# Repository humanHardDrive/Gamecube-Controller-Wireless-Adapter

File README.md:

# GameCube Wireless Controller Hub
The GameCube Wireless Controller hub allows 4 GameCube controllers to be made wireless to any GameCube controller interface. The hub functions in two halves, one to connect to the controllers, and one to connect to the console. Both halves are based on the RP2040 microcontroller and the NRF24l01 transceiver and share the same source code.

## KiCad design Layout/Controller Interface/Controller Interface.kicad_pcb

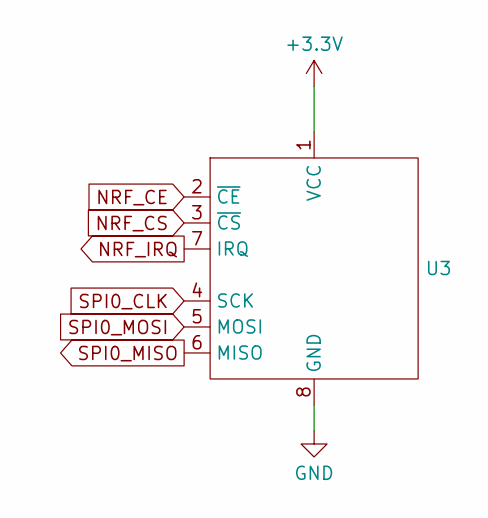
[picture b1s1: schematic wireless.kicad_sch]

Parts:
U3: GTS24-SMD

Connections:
+3.3V: U3.1 (VCC); also elsewhere on the board
GND: U3.8 (GND); also elsewhere on the board
NRF_CE: U3.2 (~CE); also elsewhere on the board
NRF_CS: U3.3 (~CS); also elsewhere on the board
NRF_IRQ: U3.7 (IRQ); also elsewhere on the board
SPI0_CLK: U3.4 (SCK); also elsewhere on the board
SPI0_MISO: U3.6 (MISO); also elsewhere on the board
SPI0_MOSI: U3.5 (MOSI); also elsewhere on the board

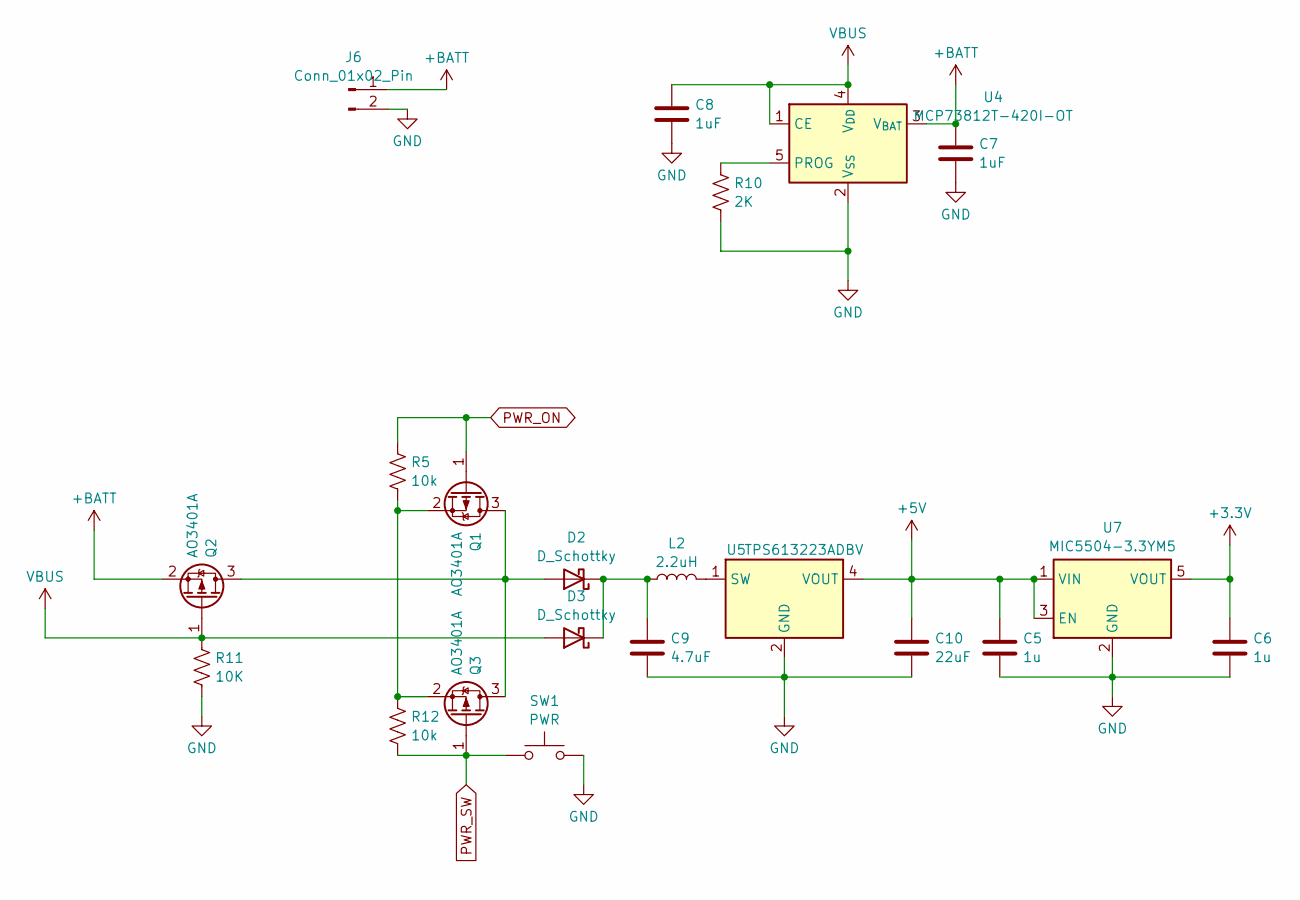
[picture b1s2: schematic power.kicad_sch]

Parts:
C5, C6: 1u; C_0603_1608Metric
C7, C8: 1uF; C_0603_1608Metric
C9: 4.7uF; C_0603_1608Metric
C10: 22uF; C_0603_1608Metric
D2, D3: D_Schottky; D_0805_2012Metric
J6: Conn_01x02_Pin; JST_PH_S2B-PH-SM4-TB_1x02-1MP_P2.00mm_Horizontal
L2: 2.2uH; L_0805_2012Metric
Q1, Q2, Q3: AO3401A; SOT-23
R5, R12: 10k; R_0603_1608Metric
R10: 2K; R_0603_1608Metric
R11: 10K; R_0603_1608Metric
SW1: PWR; Panasonic_EVQPUK_EVQPUB
U4: MCP73812T-420I-OT; SOT-23-5
U5: TPS613223ADBV; SOT-23-5
U7: MIC5504-3.3YM5; SOT-23-5

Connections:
+3.3V: C6.1, U7.5 (VOUT); also elsewhere on the board
+5V: C5.1, C10.1, U5.4 (VOUT), U7.1 (VIN), U7.3 (EN); also elsewhere on the board
+BATT: C7.1, J6.1, Q2.2 (S), U4.3 (V_{BAT})
GND: C5.2, C6.2, C7.2, C8.2, C9.2, C10.2, J6.2, R10.2, R11.1, SW1.2, U4.2 (V_{SS}), U5.2 (GND), U7.2 (GND); also elsewhere on the board
unnamed: D2.2 (A), Q1.3 (D), Q2.3 (D), Q3.3 (D)
unnamed: C9.1, D2.1 (K), D3.1 (K), L2.1
unnamed: Q1.2 (S), Q3.2 (S), R5.2, R12.1
unnamed: R10.1, U4.5 (PROG)
unnamed: L2.2, U5.1 (SW)
PWR_ON: Q1.1 (G), R5.1; also elsewhere on the board
PWR_SW: Q3.1 (G), R12.2, SW1.1; also elsewhere on the board
VBUS: C8.1, D3.2 (A), Q2.1 (G), R11.2, U4.1 (CE), U4.4 (V_{DD}); also elsewhere on the board

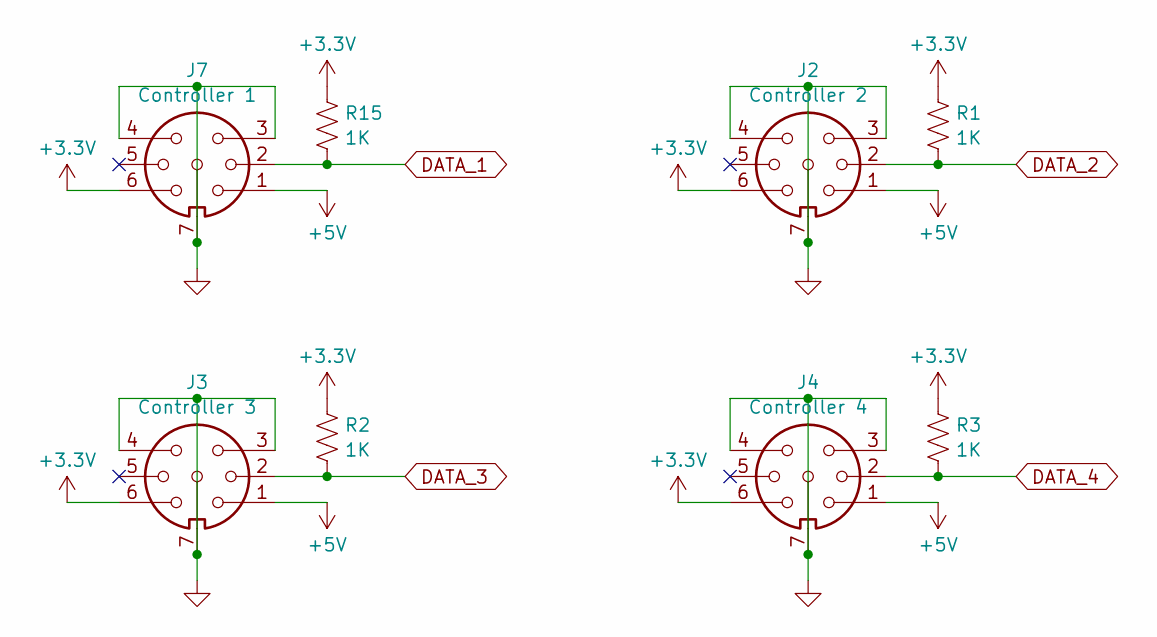
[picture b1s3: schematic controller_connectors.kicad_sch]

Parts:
J2: Controller 2; Gamecube Controller Socket
J3: Controller 3; Gamecube Controller Socket
J4: Controller 4; Gamecube Controller Socket
J7: Controller 1; Gamecube Controller Socket
R1, R2, R3, R15: 1K; R_0603_1608Metric

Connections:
+3.3V: J2.6, J3.6, J4.6, J7.6, R1.1, R2.1, R3.1, R15.1; also elsewhere on the board
+5V: J2.1, J3.1, J4.1, J7.1; also elsewhere on the board
DATA_1: J7.2, R15.2; also elsewhere on the board
DATA_2: J2.2, R1.2; also elsewhere on the board
DATA_3: J3.2, R2.2; also elsewhere on the board
DATA_4: J4.2, R3.2; also elsewhere on the board
GND: J2.3, J2.4, J2.7, J3.3, J3.4, J3.7, J4.3, J4.4, J4.7, J7.3, J7.4, J7.7; also elsewhere on the board

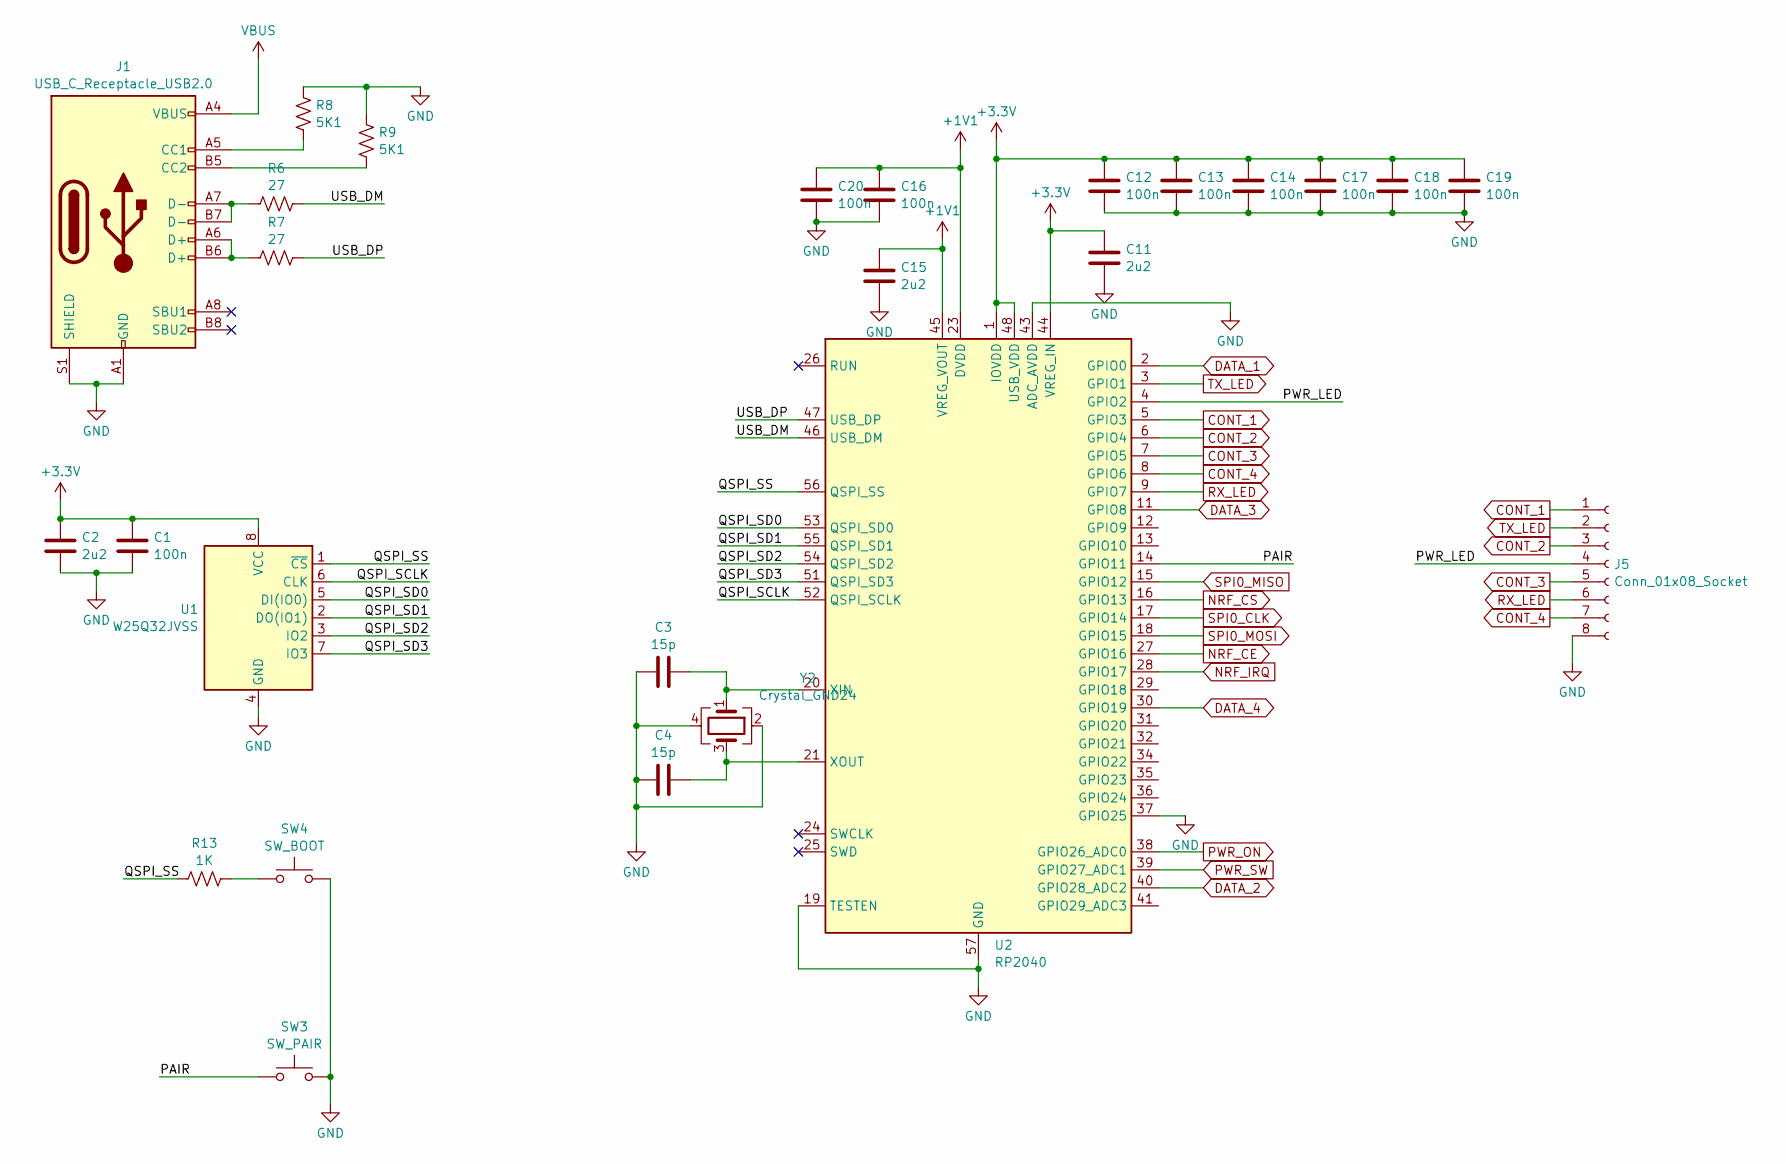
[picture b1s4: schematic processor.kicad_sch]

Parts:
C1, C12, C13, C14, C16, C17, C18, C19, C20: 100n; C_0603_1608Metric
C2, C11, C15: 2u2; C_0603_1608Metric
C3, C4: 15p; C_0603_1608Metric
J1: USB_C_Receptacle_USB2.0; USB_C_Receptacle_GCT_USB4105-xx-A_16P_TopMnt_Horizontal
J5: Conn_01x08_Socket; PinSocket_2x04_P1.00mm_Vertical_SMD
R6, R7: 27; R_0603_1608Metric
R8, R9: 5K1; R_0603_1608Metric
R13: 1K; R_0603_1608Metric
SW3: SW_PAIR; Panasonic_EVQPUK_EVQPUB
SW4: SW_BOOT; SW_SPST_TL3342
U1: W25Q32JVSS; SOIC-8_5.23x5.23mm_P1.27mm
U2: RP2040; QFN-56-1EP_7x7mm_P0.4mm_EP3.2x3.2mm
Y2: Crystal_GND24; Crystal_SMD_Abracon_ABM8G-4Pin_3.2x2.5mm

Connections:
+1V1: C15.1, C16.1, C20.1, U2.23 (DVDD), U2.45 (VREG_VOUT), U2.50 (DVDD)
+3.3V: C1.1, C2.1, C11.1, C12.1, C13.1, C14.1, C17.1, C18.1, C19.1, U1.8 (VCC), U2.1 (IOVDD), U2.10 (IOVDD), U2.22 (IOVDD), U2.33 (IOVDD), U2.42 (IOVDD), U2.44 (VREG_IN), U2.48 (USB_VDD), U2.49 (IOVDD); also elsewhere on the board
/Processor/PAIR: SW3.1, U2.14 (GPIO11)
/Processor/PWR_LED: J5.4, U2.4 (GPIO2)
/Processor/QSPI_SCLK: U1.6 (CLK), U2.52 (QSPI_SCLK)
/Processor/QSPI_SD0: U1.5 (DI(IO0)), U2.53 (QSPI_SD0)
/Processor/QSPI_SD1: U1.2 (DO(IO1)), U2.55 (QSPI_SD1)
/Processor/QSPI_SD2: U1.3 (IO2), U2.54 (QSPI_SD2)
/Processor/QSPI_SD3: U1.7 (IO3), U2.51 (QSPI_SD3)
/Processor/QSPI_SS: R13.1, U1.1 (~CS), U2.56 (QSPI_SS)
/Processor/USB_DM: R6.2, U2.46 (USB_DM)
/Processor/USB_DP: R7.2, U2.47 (USB_DP)
CONT_1: J5.1, U2.5 (GPIO3)
CONT_2: J5.3, U2.6 (GPIO4)
CONT_3: J5.5, U2.7 (GPIO5)
CONT_4: J5.7, U2.8 (GPIO6)
DATA_1: U2.2 (GPIO0); also elsewhere on the board
DATA_2: U2.40 (GPIO28_ADC2); also elsewhere on the board
DATA_3: U2.11 (GPIO8); also elsewhere on the board
DATA_4: U2.30 (GPIO19); also elsewhere on the board
GND: C1.2, C2.2, C3.2, C4.1, C11.2, C12.2, C13.2, C14.2, C15.2, C16.2, C17.2, C18.2, C19.2, C20.2, J1.A1 (GND), J1.A12 (GND), J1.B1 (GND), J1.B12 (GND), J1.S1 (SHIELD), J5.8, R8.2, R9.2, SW3.2, SW4.2, U1.4 (GND), U2.19 (TESTEN), U2.37 (GPIO25), U2.43 (ADC_AVDD), U2.57 (GND), Y2.2, Y2.4; also elsewhere on the board
NRF_CE: U2.27 (GPIO16); also elsewhere on the board
NRF_CS: U2.16 (GPIO13); also elsewhere on the board
NRF_IRQ: U2.28 (GPIO17); also elsewhere on the board
unnamed: J1.A5 (CC1), R8.1
unnamed: J1.B5 (CC2), R9.1
unnamed: J1.A6 (D+), J1.B6 (D+), R7.1
unnamed: J1.A7 (D-), J1.B7 (D-), R6.1
unnamed: R13.2, SW4.1
unnamed: C3.1, U2.20 (XIN), Y2.1
unnamed: C4.2, U2.21 (XOUT), Y2.3
PWR_ON: U2.38 (GPIO26_ADC0); also elsewhere on the board
PWR_SW: U2.39 (GPIO27_ADC1); also elsewhere on the board
RX_LED: J5.6, U2.9 (GPIO7)
SPI0_CLK: U2.17 (GPIO14); also elsewhere on the board
SPI0_MISO: U2.15 (GPIO12); also elsewhere on the board
SPI0_MOSI: U2.18 (GPIO15); also elsewhere on the board
TX_LED: J5.2, U2.3 (GPIO1)
VBUS: J1.A4 (VBUS), J1.A9 (VBUS), J1.B4 (VBUS), J1.B9 (VBUS); also elsewhere on the board

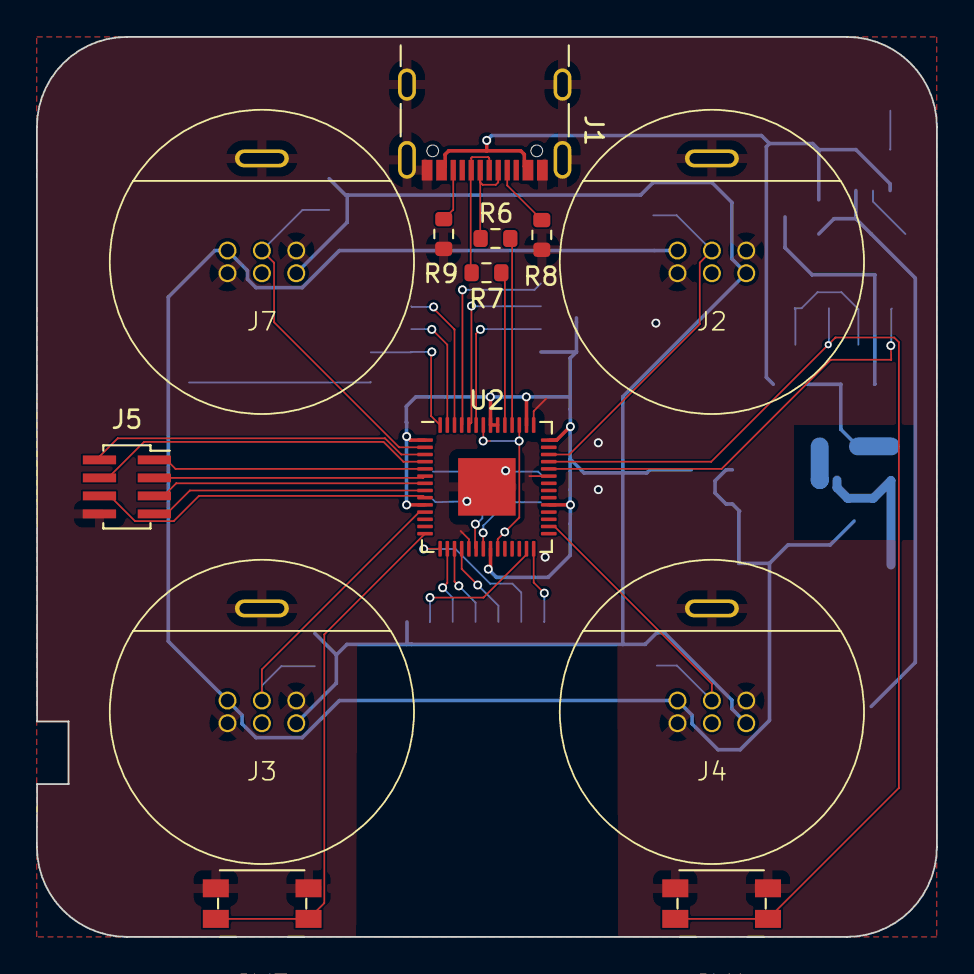
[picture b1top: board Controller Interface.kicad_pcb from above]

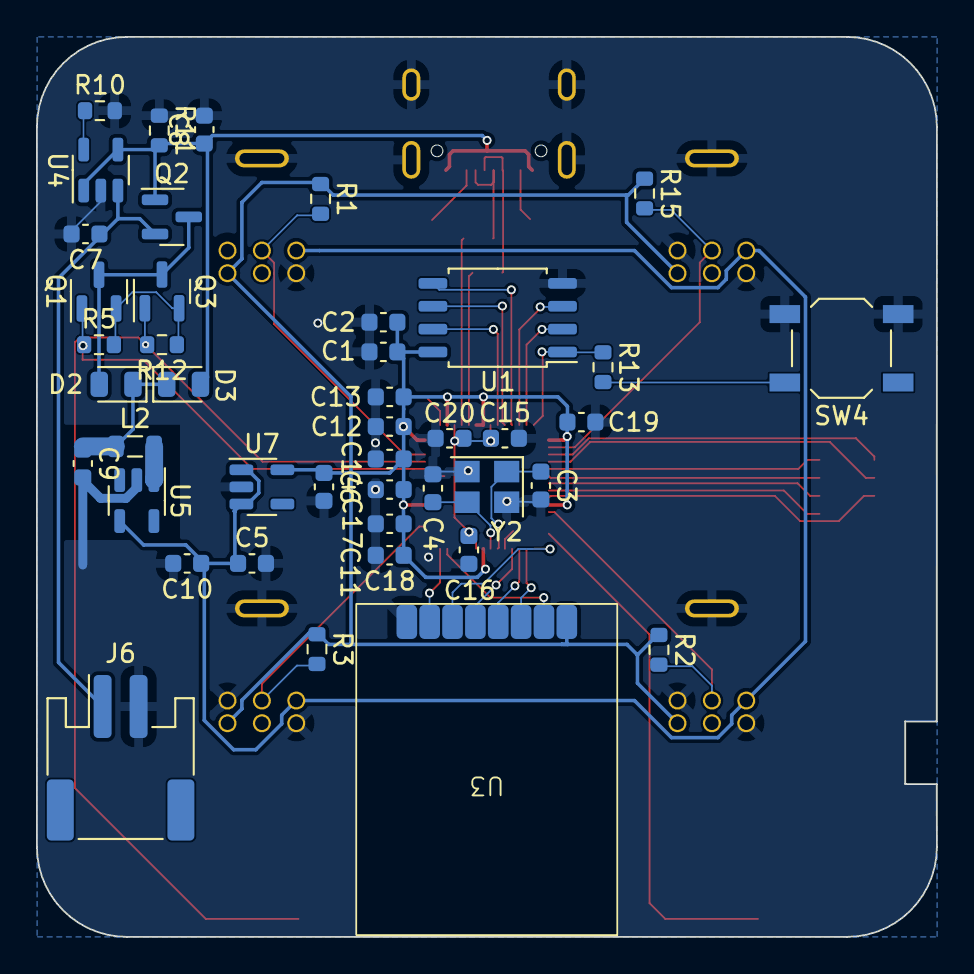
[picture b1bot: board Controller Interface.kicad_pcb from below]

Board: 2 copper layers, 50.0 x 50.0 mm, 56 parts (43 on the bottom side), 46 nets.

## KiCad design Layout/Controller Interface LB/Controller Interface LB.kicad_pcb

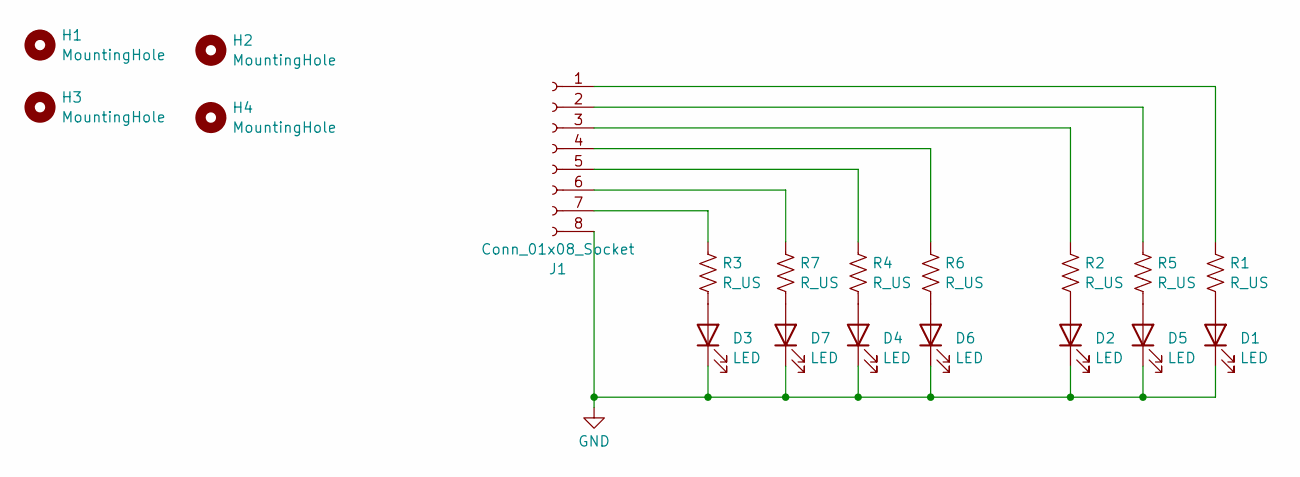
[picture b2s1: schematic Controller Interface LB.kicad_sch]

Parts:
D1, D2, D3, D4, D5, D6, D7: LED; LED_0603_1608Metric
H1, H2, H3, H4: MountingHole; MountingHole_2.2mm_M2
J1: Conn_01x08_Socket; PinSocket_2x04_P1.00mm_Vertical_SMD
R1, R2, R3, R4, R5, R6, R7: R_US; R_0603_1608Metric

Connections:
GND: D1.1 (K), D2.1 (K), D3.1 (K), D4.1 (K), D5.1 (K), D6.1 (K), D7.1 (K), J1.8
unnamed: D1.2 (A), R1.2
unnamed: D2.2 (A), R2.2
unnamed: D3.2 (A), R3.2
unnamed: D4.2 (A), R4.2
unnamed: D5.2 (A), R5.2
unnamed: D6.2 (A), R6.2
unnamed: D7.2 (A), R7.2
unnamed: J1.1, R1.1
unnamed: J1.2, R5.1
unnamed: J1.3, R2.1
unnamed: J1.4, R6.1
unnamed: J1.5, R4.1
unnamed: J1.6, R7.1
unnamed: J1.7, R3.1

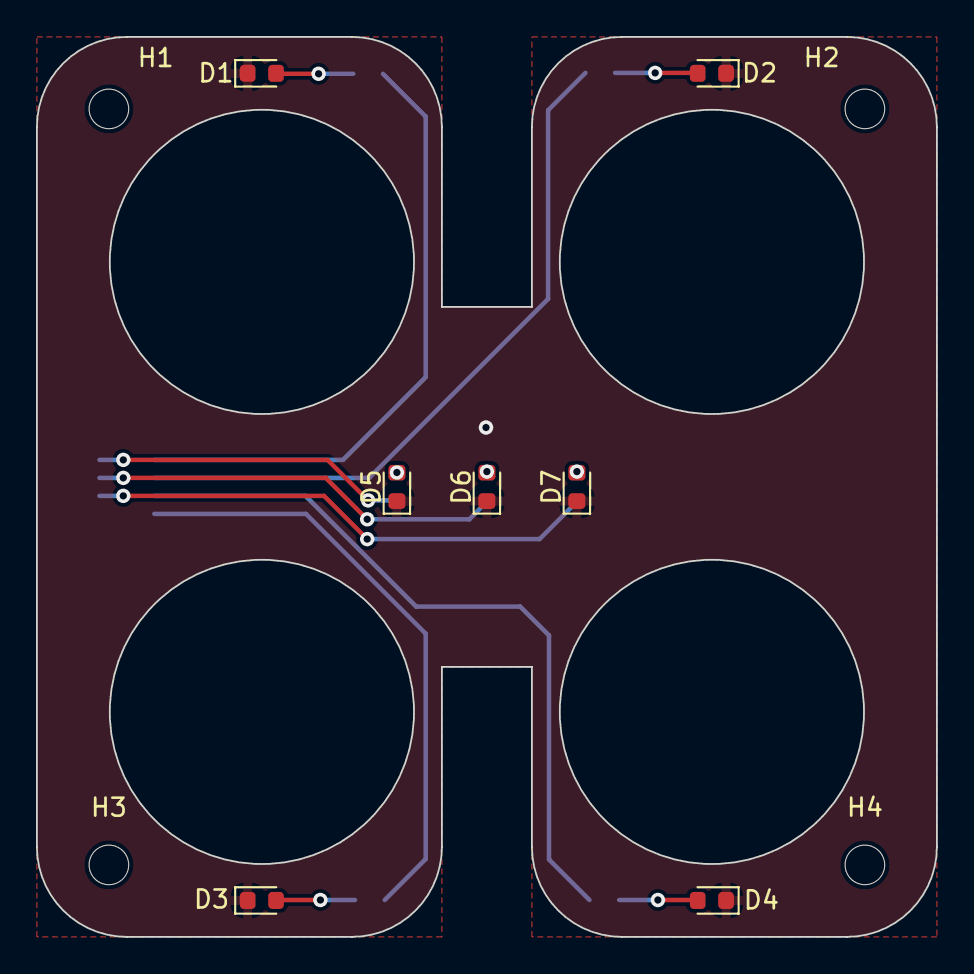
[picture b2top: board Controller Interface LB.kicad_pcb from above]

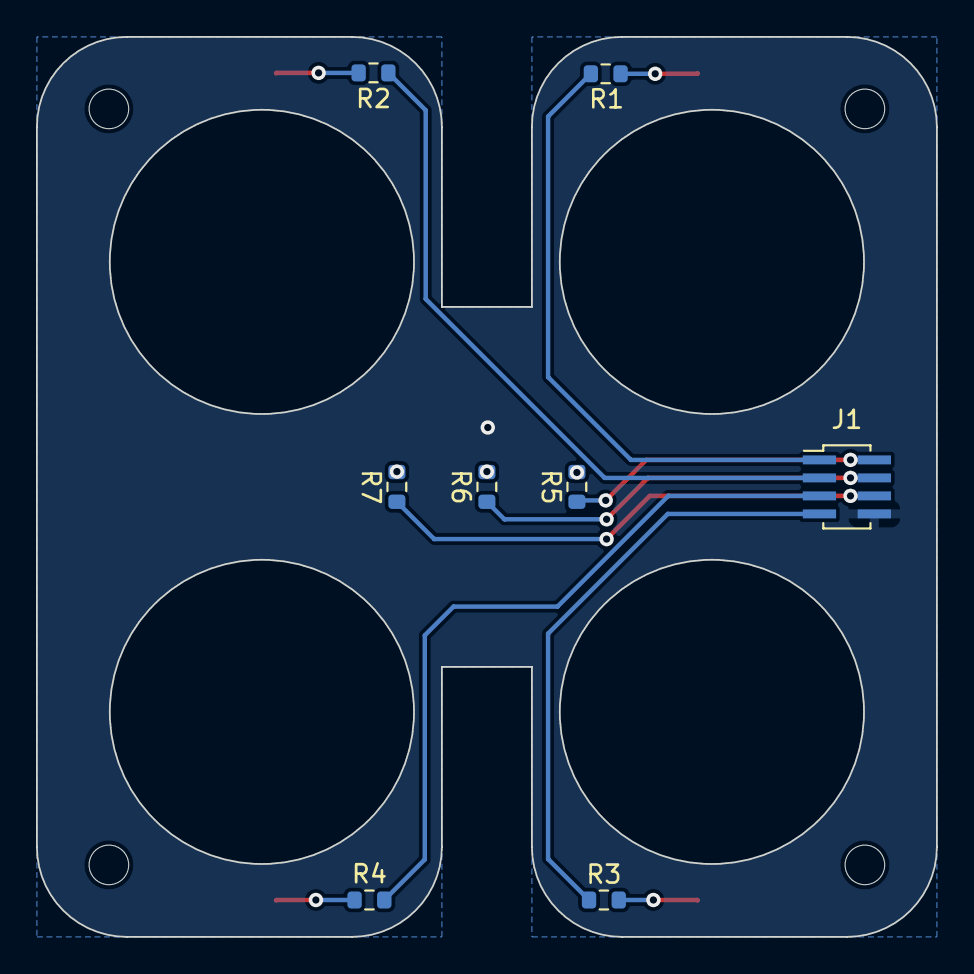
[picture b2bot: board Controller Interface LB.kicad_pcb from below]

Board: 2 copper layers, 50.0 x 50.0 mm, 19 parts (8 on the bottom side), 15 nets.

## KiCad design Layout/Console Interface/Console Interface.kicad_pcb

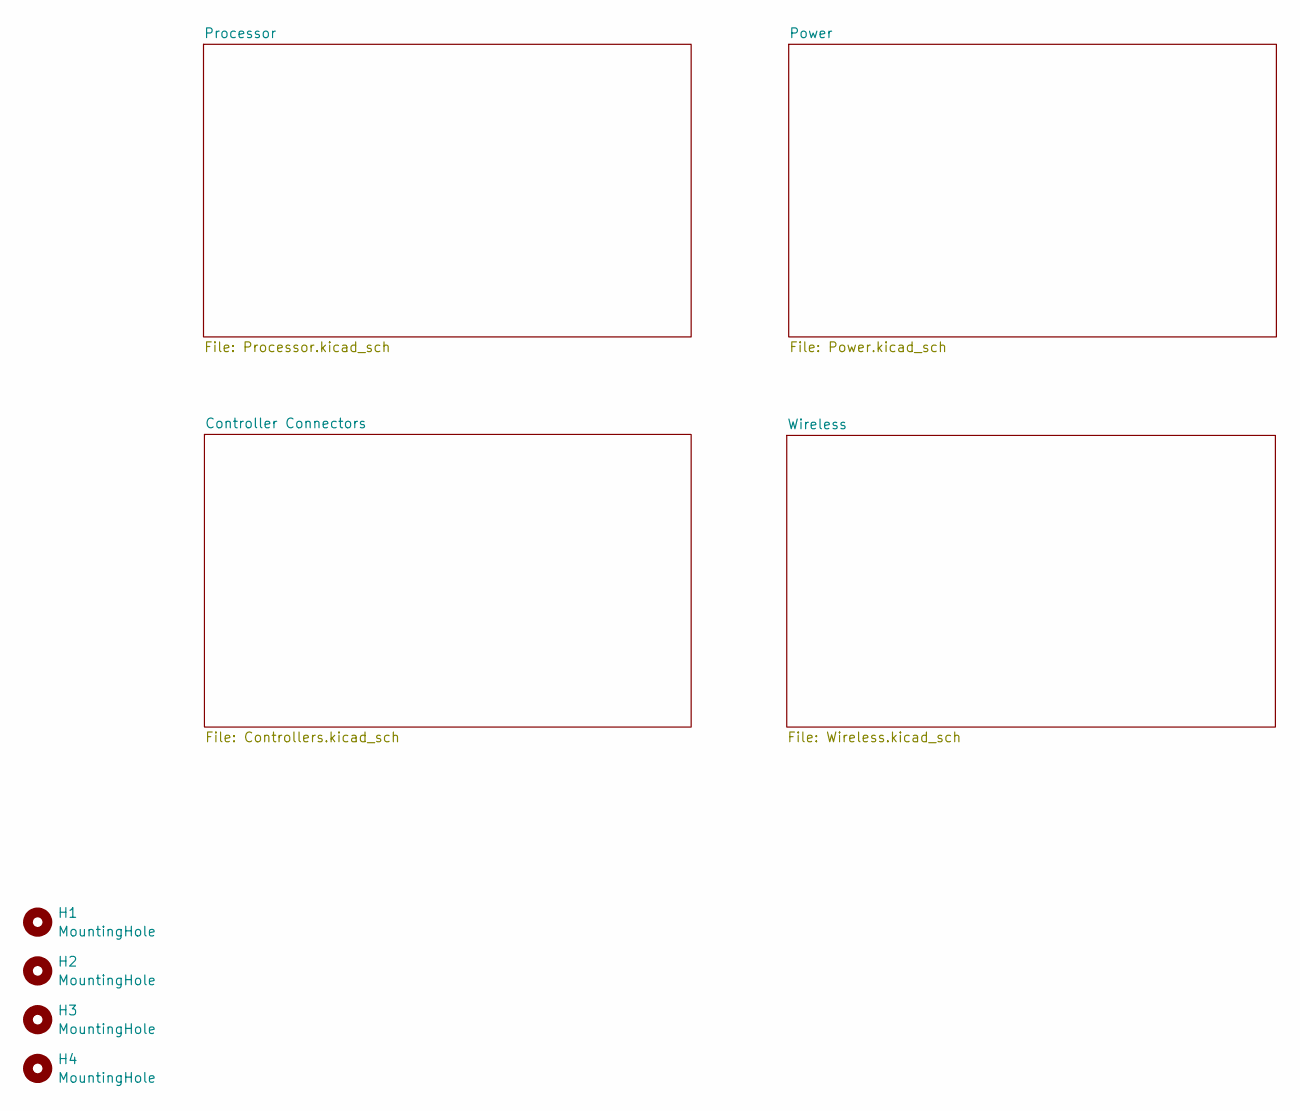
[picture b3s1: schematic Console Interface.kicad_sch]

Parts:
H1, H2, H3, H4: MountingHole; MountingHole_2.2mm_M2

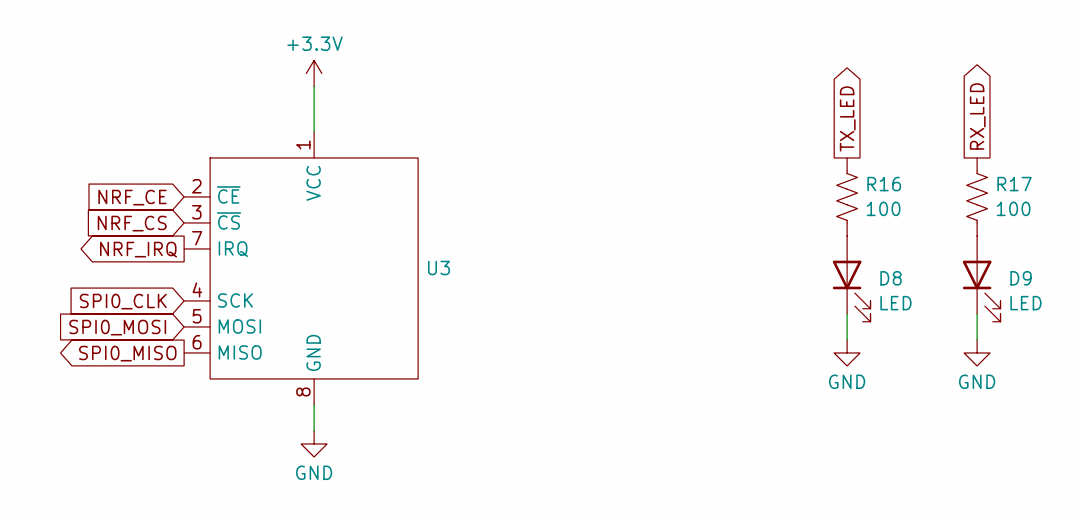
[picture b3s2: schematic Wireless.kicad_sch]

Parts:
D8, D9: LED; LED_0603_1608Metric
R16, R17: 100; R_0603_1608Metric
U3: GTS24-SMD

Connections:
+3.3V: U3.1 (VCC); also elsewhere on the board
GND: D8.1 (K), D9.1 (K), U3.8 (GND); also elsewhere on the board
NRF_CE: U3.2 (~CE); also elsewhere on the board
NRF_CS: U3.3 (~CS); also elsewhere on the board
NRF_IRQ: U3.7 (IRQ)
unnamed: D8.2 (A), R16.2
unnamed: D9.2 (A), R17.2
RX_LED: R17.1; also elsewhere on the board
SPI0_CLK: U3.4 (SCK); also elsewhere on the board
SPI0_MISO: U3.6 (MISO); also elsewhere on the board
SPI0_MOSI: U3.5 (MOSI); also elsewhere on the board
TX_LED: R16.1; also elsewhere on the board

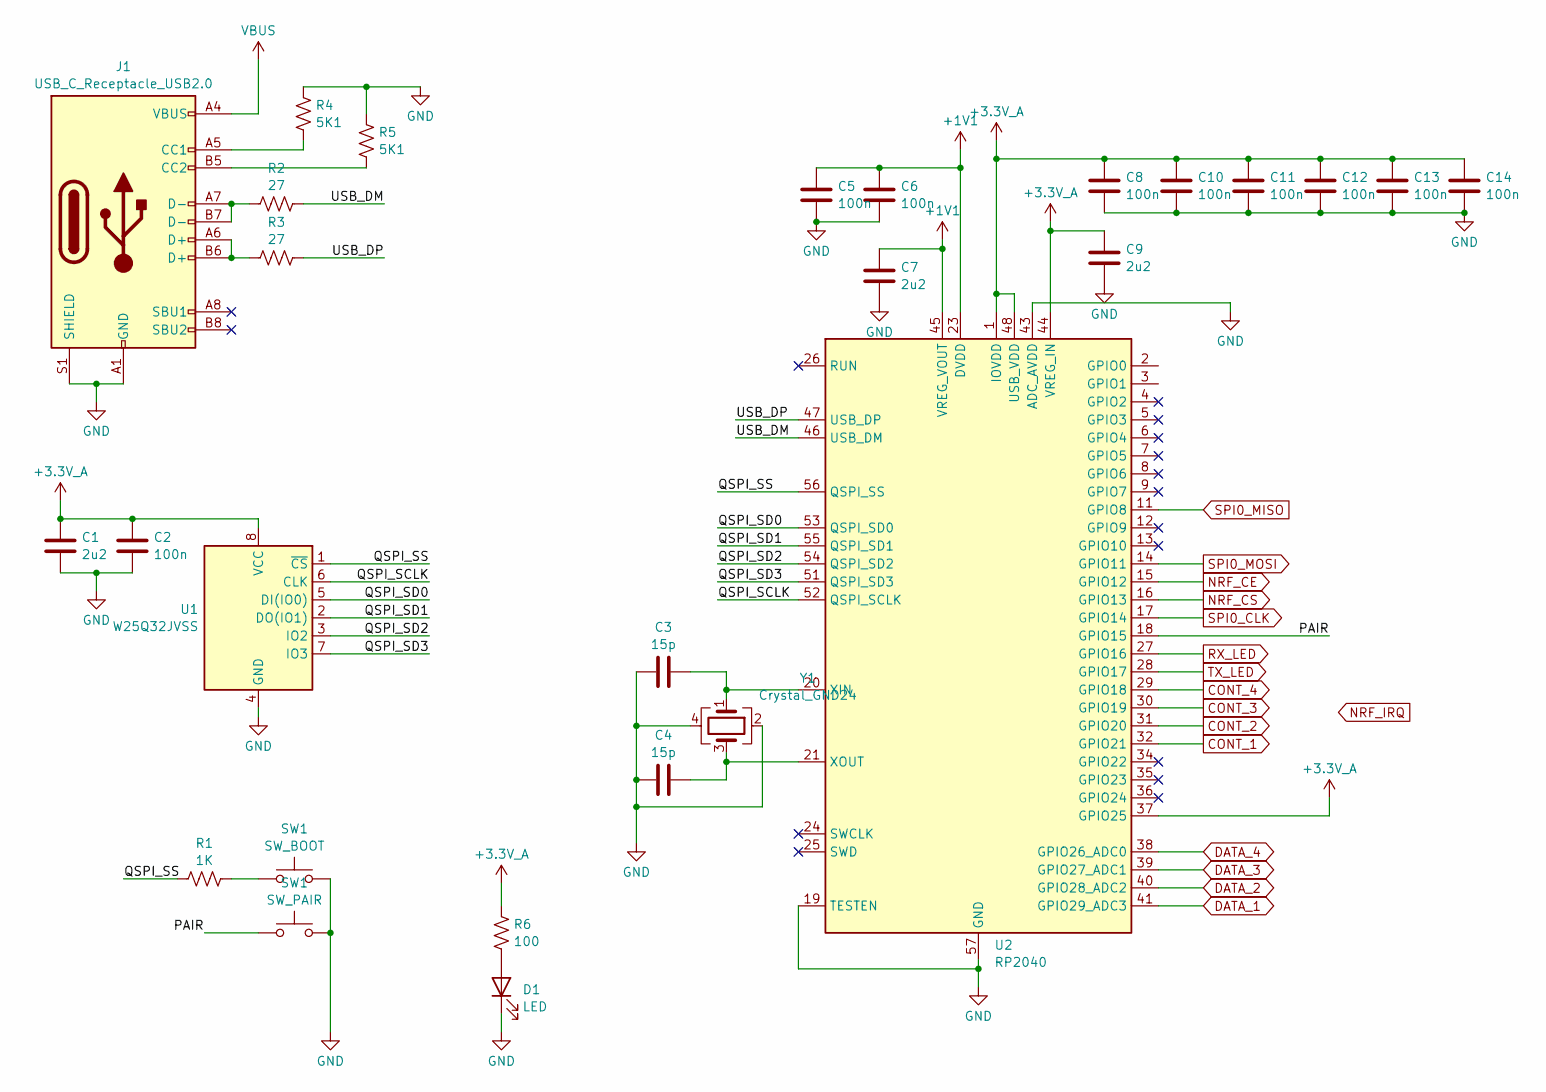
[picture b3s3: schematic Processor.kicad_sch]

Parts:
C1, C7, C9: 2u2; C_0603_1608Metric
C2, C5, C6, C8, C10, C11, C12, C13, C14: 100n; C_0603_1608Metric
C3, C4: 15p; C_0603_1608Metric
D1: LED; LED_0603_1608Metric
J1: USB_C_Receptacle_USB2.0; USB_C_Receptacle_GCT_USB4105-xx-A_16P_TopMnt_Horizontal
R1: 1K; R_0603_1608Metric
R2, R3: 27; R_0603_1608Metric
R4, R5: 5K1; R_0603_1608Metric
R6: 100; R_0603_1608Metric
SW1: SW_BOOT; SW_SPST_TL3342
U1: W25Q32JVSS; SOIC-8_5.23x5.23mm_P1.27mm
U2: RP2040; QFN-56-1EP_7x7mm_P0.4mm_EP3.2x3.2mm
Y1: Crystal_GND24; Crystal_SMD_Abracon_ABM8G-4Pin_3.2x2.5mm

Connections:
+1V1: C5.1, C6.1, C7.1, U2.23 (DVDD), U2.45 (VREG_VOUT), U2.50 (DVDD)
+3.3V_A: C1.1, C2.1, C8.1, C9.1, C10.1, C11.1, C12.1, C13.1, C14.1, R6.1, U1.8 (VCC), U2.1 (IOVDD), U2.10 (IOVDD), U2.22 (IOVDD), U2.33 (IOVDD), U2.37 (GPIO25), U2.42 (IOVDD), U2.44 (VREG_IN), U2.48 (USB_VDD), U2.49 (IOVDD); also elsewhere on the board
/Processor/QSPI_SCLK: U1.6 (CLK), U2.52 (QSPI_SCLK)
/Processor/QSPI_SD0: U1.5 (DI(IO0)), U2.53 (QSPI_SD0)
/Processor/QSPI_SD1: U1.2 (DO(IO1)), U2.55 (QSPI_SD1)
/Processor/QSPI_SD2: U1.3 (IO2), U2.54 (QSPI_SD2)
/Processor/QSPI_SD3: U1.7 (IO3), U2.51 (QSPI_SD3)
/Processor/QSPI_SS: R1.1, U1.1 (~CS), U2.56 (QSPI_SS)
/Processor/USB_DM: R2.2, U2.46 (USB_DM)
/Processor/USB_DP: R3.2, U2.47 (USB_DP)
CONT_1: U2.32 (GPIO21); also elsewhere on the board
CONT_2: U2.31 (GPIO20); also elsewhere on the board
CONT_3: U2.30 (GPIO19); also elsewhere on the board
CONT_4: U2.29 (GPIO18); also elsewhere on the board
DATA_1: U2.41 (GPIO29_ADC3); also elsewhere on the board
DATA_2: U2.40 (GPIO28_ADC2); also elsewhere on the board
DATA_3: U2.39 (GPIO27_ADC1); also elsewhere on the board
DATA_4: U2.38 (GPIO26_ADC0); also elsewhere on the board
GND: C1.2, C2.2, C3.2, C4.1, C5.2, C6.2, C7.2, C8.2, C9.2, C10.2, C11.2, C12.2, C13.2, C14.2, D1.1 (K), J1.A1 (GND), J1.A12 (GND), J1.B1 (GND), J1.B12 (GND), J1.S1 (SHIELD), R4.2, R5.2, SW1.2, U1.4 (GND), U2.19 (TESTEN), U2.43 (ADC_AVDD), U2.57 (GND), Y1.2, Y1.4; also elsewhere on the board
NRF_CE: U2.15 (GPIO12); also elsewhere on the board
NRF_CS: U2.16 (GPIO13); also elsewhere on the board
unnamed: D1.2 (A), R6.2
unnamed: J1.A5 (CC1), R4.1
unnamed: J1.B5 (CC2), R5.1
unnamed: J1.A6 (D+), J1.B6 (D+), R3.1
unnamed: J1.A7 (D-), J1.B7 (D-), R2.1
unnamed: C3.1, U2.20 (XIN), Y1.1
unnamed: C4.2, U2.21 (XOUT), Y1.3
RX_LED: U2.27 (GPIO16); also elsewhere on the board
SPI0_CLK: U2.17 (GPIO14); also elsewhere on the board
SPI0_MISO: U2.11 (GPIO8); also elsewhere on the board
SPI0_MOSI: U2.14 (GPIO11); also elsewhere on the board
TX_LED: U2.28 (GPIO17); also elsewhere on the board
VBUS: J1.A4 (VBUS), J1.A9 (VBUS), J1.B4 (VBUS), J1.B9 (VBUS); also elsewhere on the board

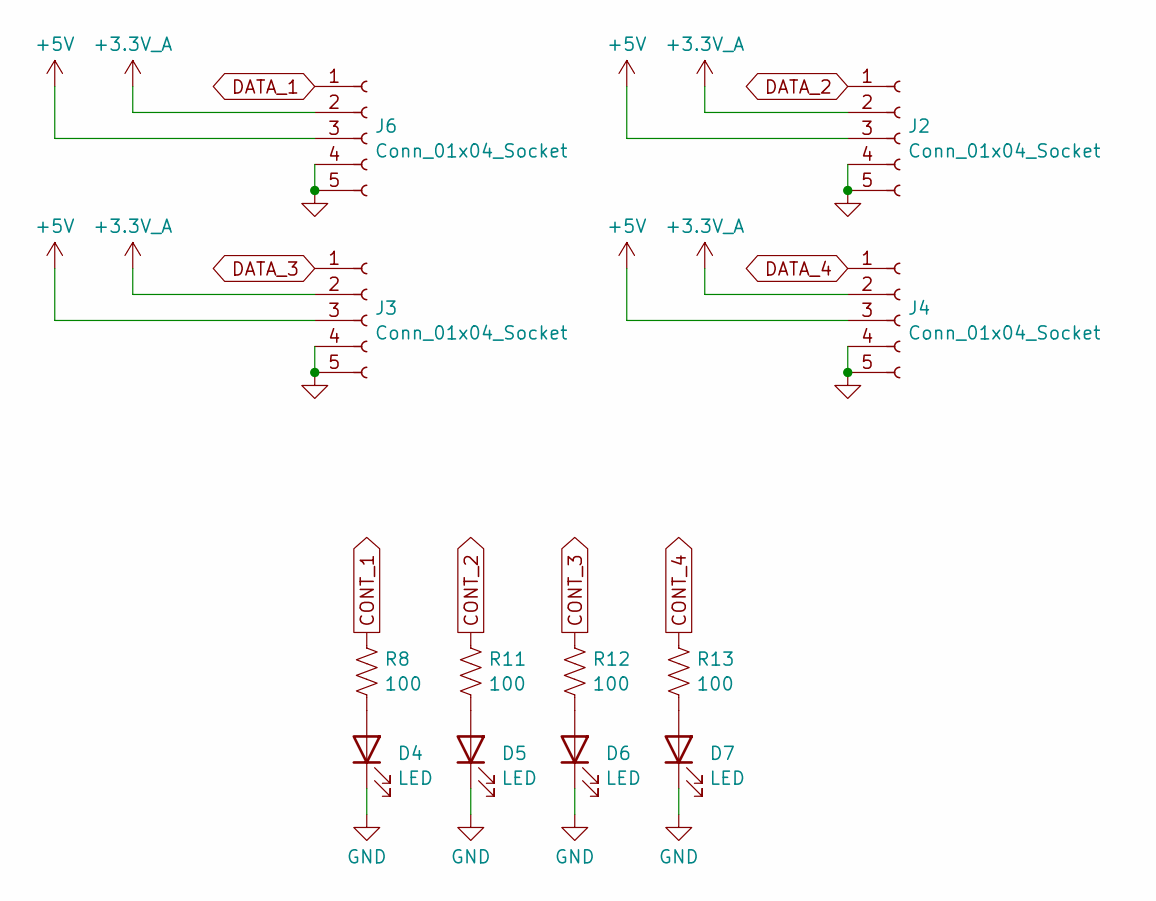
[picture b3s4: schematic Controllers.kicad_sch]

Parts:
D4, D5, D6, D7: LED; LED_0603_1608Metric
J2, J3, J4, J6: Conn_01x04_Socket; JST_GH_BM05B-GHS-TBT_1x05-1MP_P1.25mm_Vertical
R8, R11, R12, R13: 100; R_0603_1608Metric

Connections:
+3.3V_A: J2.2, J3.2, J4.2, J6.2; also elsewhere on the board
+5V: J2.3, J3.3, J4.3, J6.3; also elsewhere on the board
CONT_1: R8.1; also elsewhere on the board
CONT_2: R11.1; also elsewhere on the board
CONT_3: R12.1; also elsewhere on the board
CONT_4: R13.1; also elsewhere on the board
DATA_1: J6.1; also elsewhere on the board
DATA_2: J2.1; also elsewhere on the board
DATA_3: J3.1; also elsewhere on the board
DATA_4: J4.1; also elsewhere on the board
GND: D4.1 (K), D5.1 (K), D6.1 (K), D7.1 (K), J2.4, J2.5, J3.4, J3.5, J4.4, J4.5, J6.4, J6.5; also elsewhere on the board
unnamed: D4.2 (A), R8.2
unnamed: D5.2 (A), R11.2
unnamed: D6.2 (A), R12.2
unnamed: D7.2 (A), R13.2

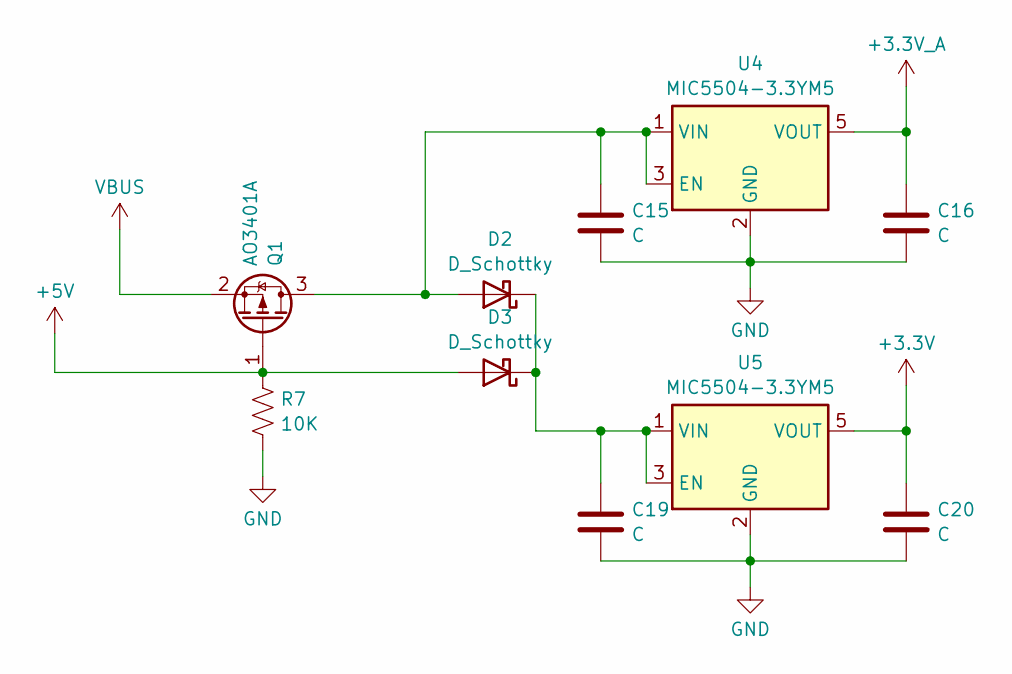
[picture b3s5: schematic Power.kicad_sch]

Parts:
C15, C16, C19, C20: C; C_0603_1608Metric
D2, D3: D_Schottky; D_0603_1608Metric
Q1: AO3401A; SOT-23
R7: 10K; R_0603_1608Metric
U4, U5: MIC5504-3.3YM5; SOT-23-5

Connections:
+3.3V: C20.1, U5.5 (VOUT); also elsewhere on the board
+3.3V_A: C16.1, U4.5 (VOUT); also elsewhere on the board
+5V: D3.2 (A), Q1.1 (G), R7.2; also elsewhere on the board
GND: C15.2, C16.2, C19.2, C20.2, R7.1, U4.2 (GND), U5.2 (GND); also elsewhere on the board
unnamed: C15.1, D2.2 (A), Q1.3 (D), U4.1 (VIN), U4.3 (EN)
unnamed: C19.1, D2.1 (K), D3.1 (K), U5.1 (VIN), U5.3 (EN)
VBUS: Q1.2 (S); also elsewhere on the board

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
